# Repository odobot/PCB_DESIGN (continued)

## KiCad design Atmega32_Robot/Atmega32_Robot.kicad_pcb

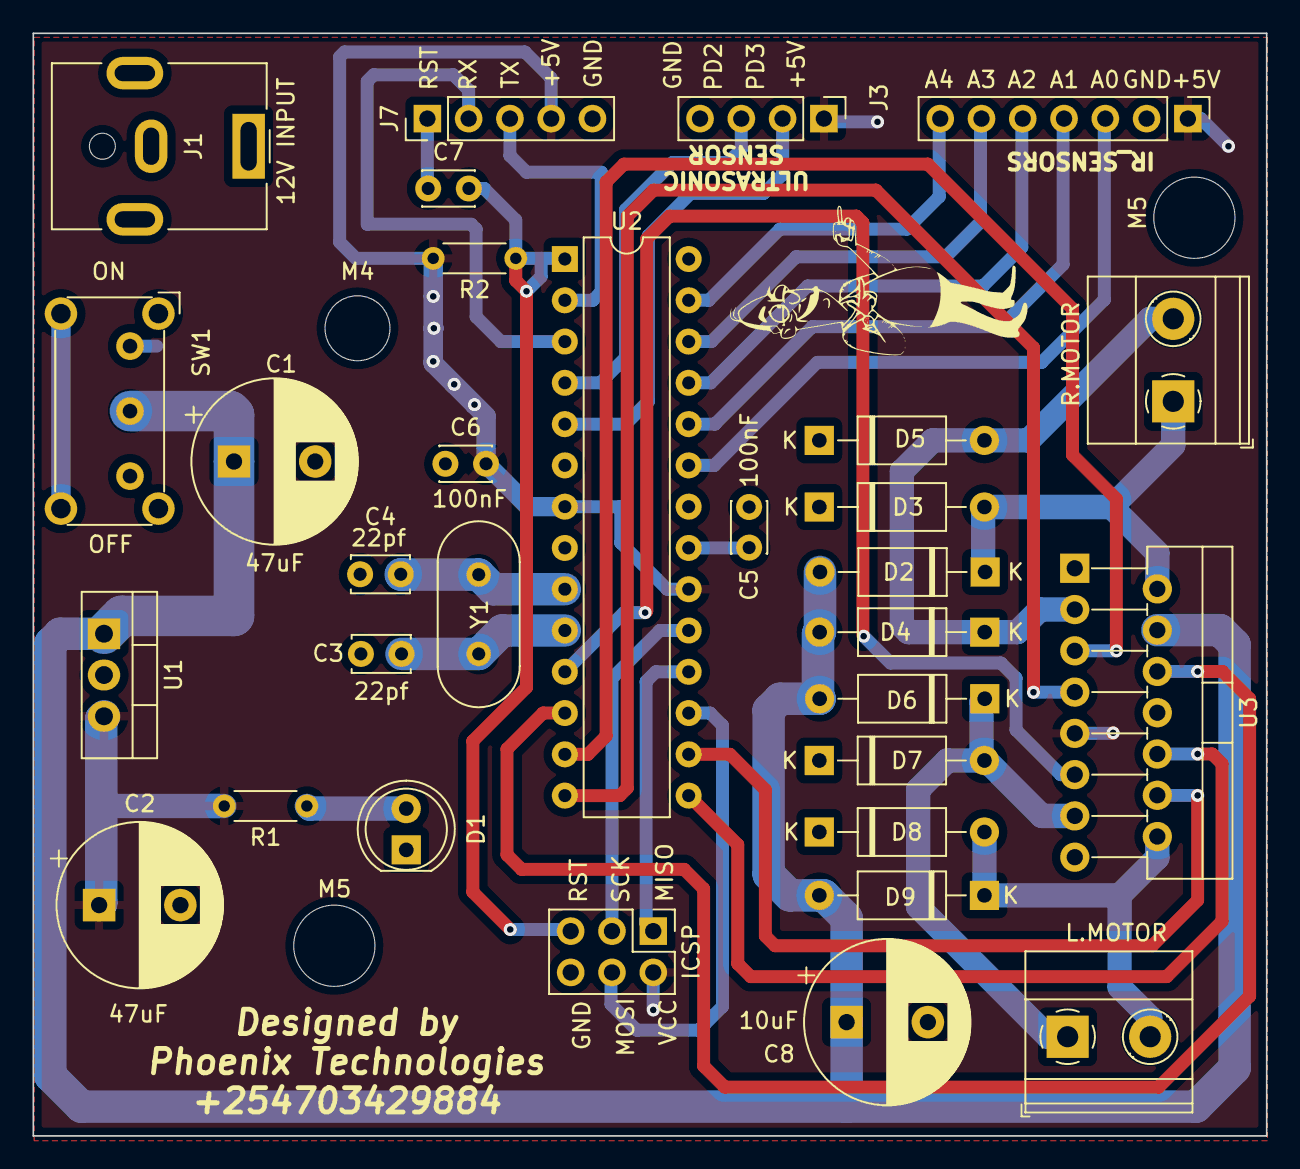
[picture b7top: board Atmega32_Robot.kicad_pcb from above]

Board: 2 copper layers, 75.9 x 67.8 mm, 35 parts (0 on the bottom side), 32 nets.

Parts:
C1, C2: 47uF; CP_Radial_D10.0mm_P5.00mm
C3, C4: 22pf; C_Disc_D3.4mm_W2.1mm_P2.50mm
C5, C6, C7: 100nF; C_Disc_D3.0mm_W2.0mm_P2.50mm
C8: 10uF; CP_Radial_D10.0mm_P5.00mm
Conn_01x07_Male: Conn_01x07_Male; PinHeader_1x07_P2.54mm_Vertical
D1: LED; LED_D5.0mm
D2, D3, D4, D5, D6, D7, D8, D9: DIODE; D_A-405_P10.16mm_Horizontal
G: LOGO; cheech
ICSP: Conn_02x03_Odd_Even; PinHeader_2x03_P2.54mm_Vertical
J1: Barrel_Jack_MountingPin; BarrelJack_CUI_PJ-063AH_Horizontal
J3: Conn_01x04_Male; PinHeader_1x04_P2.54mm_Vertical
J7: Conn_01x05_Male; PinHeader_1x05_P2.54mm_Vertical
L.MOTOR: L.MOTOR; TerminalBlock_Phoenix_MKDS-1,5-2-5.08_1x02_P5.08mm_Horizont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
M4: MountingHole_4mm; MountingHole_2.5mm
M5, M5#2: MountingHole_5mm; MountingHole_2.5mm
R1, R2: 10K; R_Axial_DIN0204_L3.6mm_D1.6mm_P5.08mm_Horizontal
R.MOTOR: R.MOTOR; TerminalBlock_Phoenix_MKDS-1,5-2-5.08_1x02_P5.08mm_Horizont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
SW1: SW_DIP_x01; SW_E-Switch_EG1224_SPDT_Angled
U1: LM78M05_TO220; TO-220-3_Vertical
U2: ATmega328P-P; DIP-28_W7.62mm
U3: L298N; TO-220-15_P2.54x2.54mm_StaggerOdd_Lead4.58mm_Vertical
Y1: 16MHZ; Crystal_HC49-4H_Vertical

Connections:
12V: J1.1, SW1.1
+5V: C2.1, C6.2, Conn_01x07_Male.1, ICSP.2, J3.1, J7.4, R1.2, R2.2, U1.3 (VO), U2.7 (VCC), U2.20 (AVCC), U3.9 (Vss)
+12V: C1.1, C8.1, D2.2 (K), D4.2 (K), D6.2 (K), D9.2 (K), SW1.2, U1.1 (VI), U3.4 (Vs)
A0: Conn_01x07_Male.3, U2.23 (PC0)
A1: Conn_01x07_Male.4, U2.24 (PC1)
A2: Conn_01x07_Male.5, U2.25 (PC2)
A3: Conn_01x07_Male.6, U2.26 (PC3)
A4: Conn_01x07_Male.7, U2.27 (PC4)
ECHO: J3.3, U2.4 (PD2)
EnA: U2.12 (PD6), U3.6 (EnA)
EnB: U2.11 (PD5), U3.11 (EnB)
GND: C2.2, C3.1, C4.1, C5.1, C6.1, C8.2, Conn_01x07_Male.2, D1.1 (K), D3.1 (A), D5.1 (A), D7.1 (A), D8.1 (A), ICSP.6, J1.2, J1.MP (MountPin), J3.4, J7.5, SW1.3, U1.2 (GND), U2.8 (GND), U2.22 (GND), U3.1 (SENSE_A), U3.8 (GND), U3.15 (SENSE_B)
IN1: U2.13 (PD7), U3.5 (IN1)
IN2: U2.14 (PB0), U3.7 (IN2)
IN3: U2.15 (PB1), U3.10 (IN3)
IN4: U2.16 (PB2), U3.12 (IN4)
MISO: ICSP.1, U2.18 (PB4)
MOSI: ICSP.4, U2.17 (PB3)
unnamed: C5.2, U2.21 (AREF)
unnamed: C7.1, J7.1
unnamed: D1.2 (A), R1.1
unnamed: D2.1 (A), D3.2 (K), R.MOTOR.1, U3.2 (OUT1)
unnamed: D4.1 (A), D5.2 (K), R.MOTOR.2, U3.3 (OUT2)
unnamed: D6.1 (A), D7.2 (K), L.MOTOR.1, U3.13 (OUT3)
unnamed: D8.2 (K), D9.1 (A), L.MOTOR.2, U3.14 (OUT4)
PB6: C4.2, U2.9 (XTAL1/PB6), Y1.2
PB7: C3.2, U2.10 (XTAL2/PB7), Y1.1
RESET: C7.2, ICSP.5, R2.1, U2.1 (~RESET/PC6)
RX: J7.2, U2.3 (PD1)
SCK: ICSP.3, U2.19 (PB5)
TRIG: J3.2, U2.5 (PD3)
TX: J7.3, U2.2 (PD0)

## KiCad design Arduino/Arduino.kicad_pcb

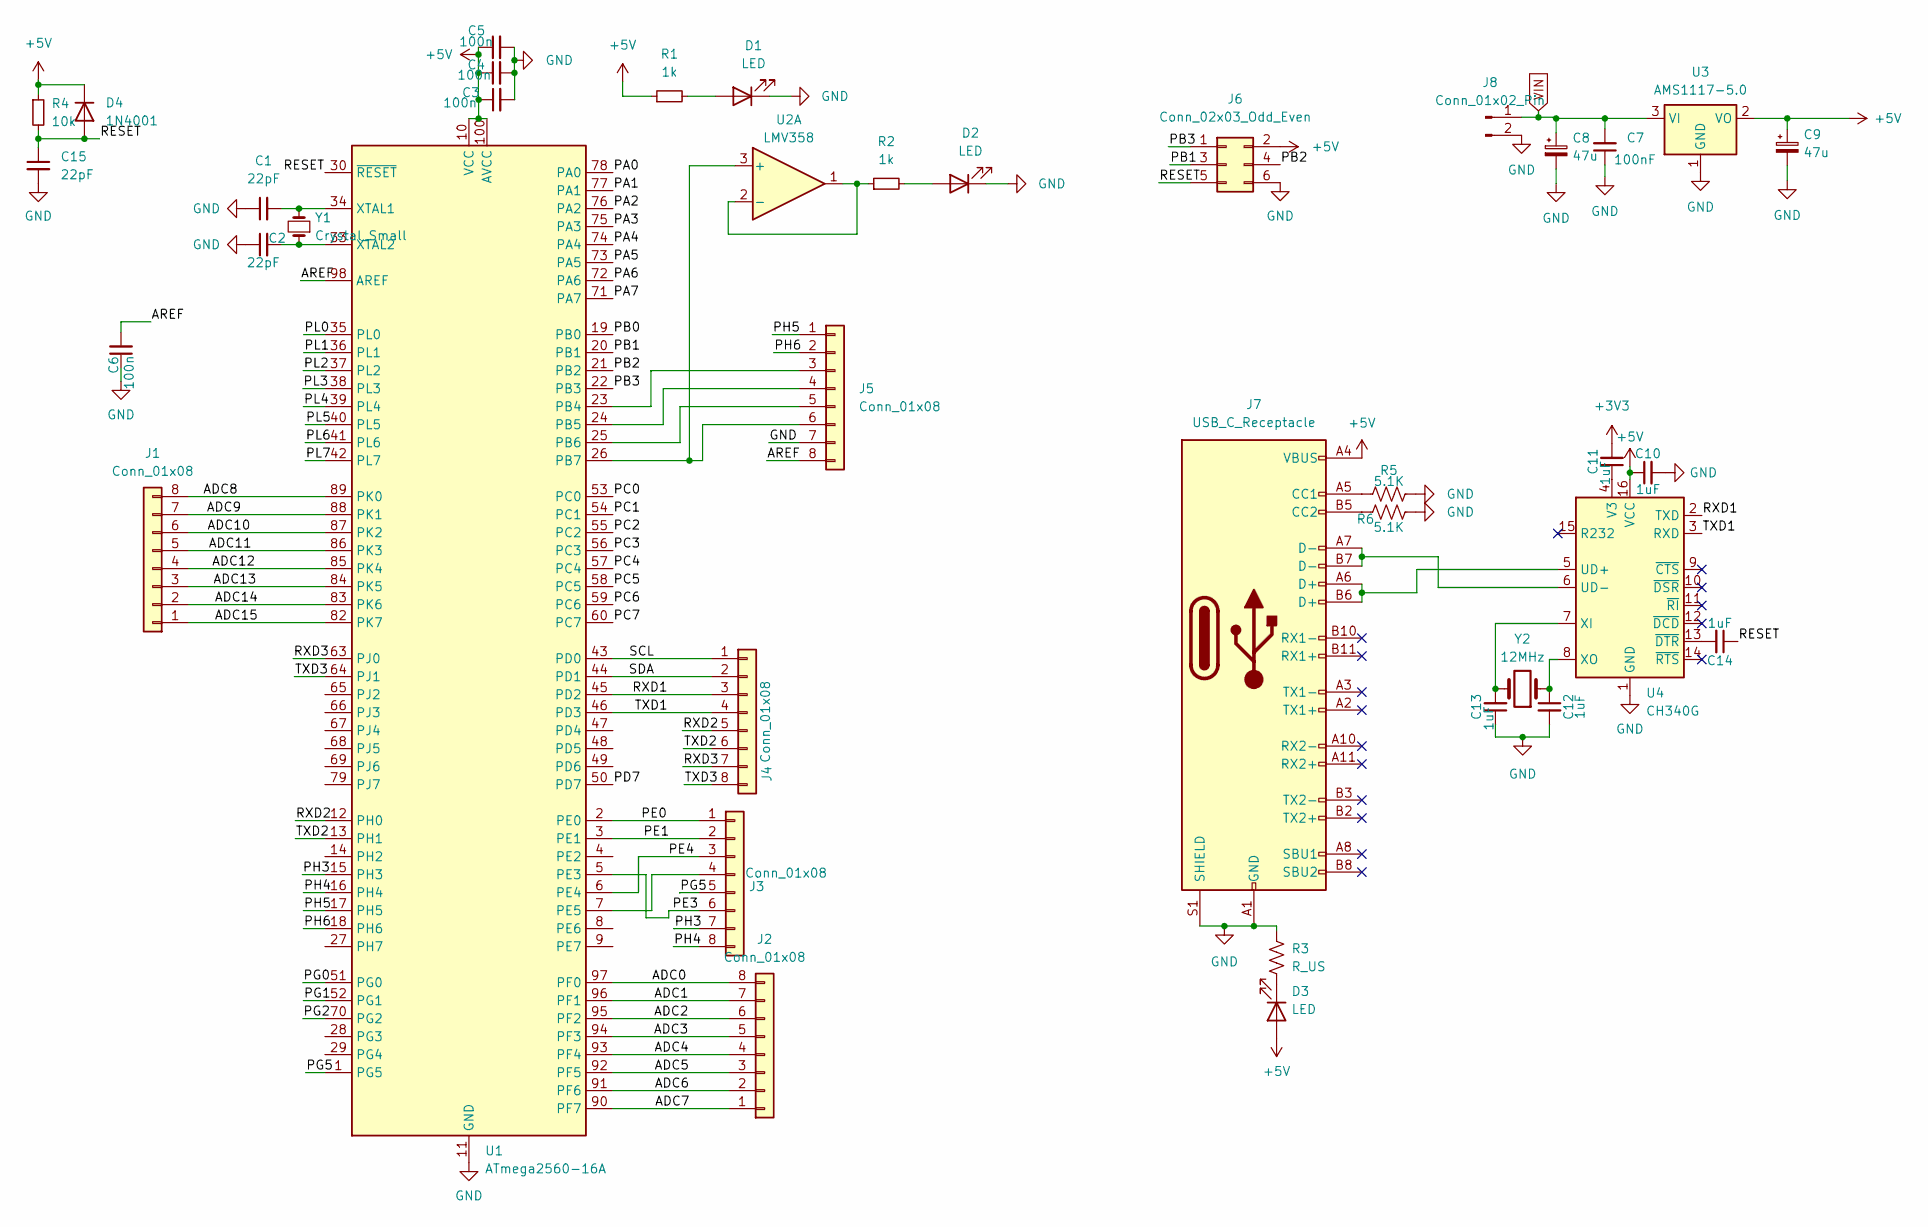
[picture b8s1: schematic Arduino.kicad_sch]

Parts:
C1, C2, C15: 22pF; C_0402_1005Metric
C3, C4, C5, C6: 100n; C_0402_1005Metric
C7: 100nF; C_0402_1005Metric
C8, C9: 47u; CP_Elec_4x3.9
C10, C11, C12, C13, C14: 1uF; C_0402_1005Metric
D1, D2, D3: LED; LED_0402_1005Metric
D4: 1N4001; D_0402_1005Metric
J1, J2, J3, J4, J5: Conn_01x08; PinSocket_1x08_P2.54mm_Vertical
J6: Conn_02x03_Odd_Even; PinSocket_2x03_P2.54mm_Vertical
J7: USB_C_Receptacle; USB_C_Receptacle_Palconn_UTC16-G
J8: Conn_01x02_Pin; JST_XA_B02B-XASK-1_1x02_P2.50mm_Vertical
R1, R2: 1k; R_0402_1005Metric
R3: R_US; R_0402_1005Metric
R4: 10k; R_0402_1005Metric
R5, R6: 5.1K; R_0402_1005Metric
U1: ATmega2560-16A; TQFP-100_14x14mm_P0.5mm
U2: LMV358; DIP-8_W7.62mm_SMDSocket_SmallPads
U3: AMS1117-5.0; SOT-223-3_TabPin2
U4: CH340G; SOIC-16_3.9x9.9mm_P1.27mm
Y1: Crystal_Small; Crystal_SMD_2012-2Pin_2.0x1.2mm
Y2: 12MHz; Crystal_SMD_2012-2Pin_2.0x1.2mm

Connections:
+3V3: C11.2; also elsewhere on the board
+5V: C3.1, C4.1, C5.1, C9.1, C10.1, D3.2 (A), D4.1 (K), J6.2, J7.A4 (VBUS), J7.A9 (VBUS), J7.B4 (VBUS), J7.B9 (VBUS), R1.1, R4.1, U1.10 (VCC), U1.31 (VCC), U1.61 (VCC), U1.80 (VCC), U1.100 (AVCC), U3.2 (VO), U4.16 (VCC)
/ADC0: J2.8, U1.97 (PF0)
/ADC1: J2.7, U1.96 (PF1)
/ADC2: J2.6, U1.95 (PF2)
/ADC3: J2.5, U1.94 (PF3)
/ADC4: J2.4, U1.93 (PF4)
/ADC5: J2.3, U1.92 (PF5)
/ADC6: J2.2, U1.91 (PF6)
/ADC7: J2.1, U1.90 (PF7)
/ADC8: J1.8, U1.89 (PK0)
/ADC9: J1.7, U1.88 (PK1)
/ADC10: J1.6, U1.87 (PK2)
/ADC11: J1.5, U1.86 (PK3)
/ADC12: J1.4, U1.85 (PK4)
/ADC13: J1.3, U1.84 (PK5)
/ADC14: J1.2, U1.83 (PK6)
/ADC15: J1.1, U1.82 (PK7)
/AREF: C6.2, J5.8, U1.98 (AREF)
/PA0: U1.78 (PA0)
/PA1: U1.77 (PA1)
/PA2: U1.76 (PA2)
/PA3: U1.75 (PA3)
/PA4: U1.74 (PA4)
/PA5: U1.73 (PA5)
/PA6: U1.72 (PA6)
/PA7: U1.71 (PA7)
/PB0: U1.19 (PB0)
/PB1: J6.3, U1.20 (PB1)
/PB2: J6.4, U1.21 (PB2)
/PB3: J6.1, U1.22 (PB3)
/PC0: U1.53 (PC0)
/PC1: U1.54 (PC1)
/PC2: U1.55 (PC2)
/PC3: U1.56 (PC3)
/PC4: U1.57 (PC4)
/PC5: U1.58 (PC5)
/PC6: U1.59 (PC6)
/PC7: U1.60 (PC7)
/PD7: U1.50 (PD7)
/PE0: J3.1, U1.2 (PE0)
/PE1: J3.2, U1.3 (PE1)
/PE3: J3.6, U1.5 (PE3)
/PE4: J3.3, U1.6 (PE4)
/PG0: U1.51 (PG0)
/PG1: U1.52 (PG1)
/PG2: U1.70 (PG2)
/PG5: J3.5, U1.1 (PG5)
/PH3: J3.7, U1.15 (PH3)
/PH4: J3.8, U1.16 (PH4)
/PH5: J5.1, U1.17 (PH5)
/PH6: J5.2, U1.18 (PH6)
/PL0: U1.35 (PL0)
/PL1: U1.36 (PL1)
/PL2: U1.37 (PL2)
/PL3: U1.38 (PL3)
/PL4: U1.39 (PL4)
/PL5: U1.40 (PL5)
/PL6: U1.41 (PL6)
/PL7: U1.42 (PL7)
/RESET: C14.1, C15.1, D4.2 (A), J6.5, R4.2, U1.30 (~RESET)
/RXD1: J4.3, U1.45 (PD2), U4.2 (TXD)
/RXD2: J4.5, U1.12 (PH0)
/RXD3: J4.7, U1.63 (PJ0)
/SCL: J4.1, U1.43 (PD0)
/SDA: J4.2, U1.44 (PD1)
/TXD1: J4.4, U1.46 (PD3), U4.3 (RXD)
/TXD2: J4.6, U1.13 (PH1)
/TXD3: J4.8, U1.64 (PJ1)
GND: C1.1, C2.1, C3.2, C4.2, C5.2, C6.1, C7.1, C8.2, C9.2, C10.2, C12.2, C13.1, C15.2, D1.1 (K), D2.1 (K), J5.7, J6.6, J7.A1 (GND), J7.A12 (GND), J7.B1 (GND), J7.B12 (GND), J7.S1 (SHIELD), J8.2, R3.1, R5.2, R6.2, U1.11 (GND), U1.32 (GND), U1.62 (GND), U1.81 (GND), U1.99 (GND), U3.1 (GND), U4.1 (GND); also elsewhere on the board
unnamed: D1.2 (A), R1.2
unnamed: D2.2 (A), R2.2
unnamed: D3.1 (K), R3.2
unnamed: J3.4, U1.7 (PE5)
unnamed: J5.3, U1.23 (PB4)
unnamed: J5.4, U1.24 (PB5)
unnamed: J5.5, U1.25 (PB6)
unnamed: J5.6, U1.26 (PB7), U2.3 (+)
unnamed: J7.A5 (CC1), R5.1
unnamed: J7.B5 (CC2), R6.1
unnamed: C1.2, U1.34 (XTAL1), Y1.2
unnamed: C2.2, U1.33 (XTAL2), Y1.1
unnamed: R2.1, U2.1, U2.2 (-)
unnamed: J7.A6 (D+), J7.B6 (D+), U4.5 (UD+)
unnamed: J7.A7 (D-), J7.B7 (D-), U4.6 (UD-)
unnamed: C11.1, U4.4 (V3)
unnamed: C13.2, U4.7 (XI), Y2.2
unnamed: C12.1, U4.8 (XO), Y2.1
unnamed: C14.2, U4.13 (~DTR)
VIN: C7.2, C8.1, J8.1, U3.3 (VI); also elsewhere on the board

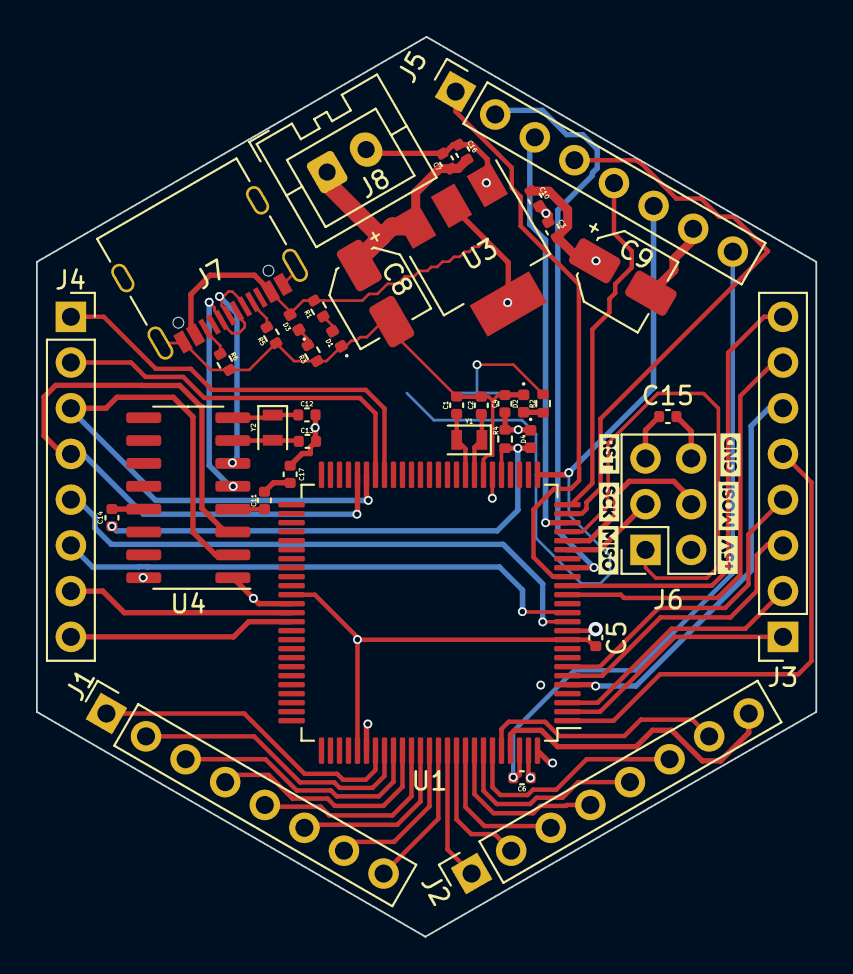
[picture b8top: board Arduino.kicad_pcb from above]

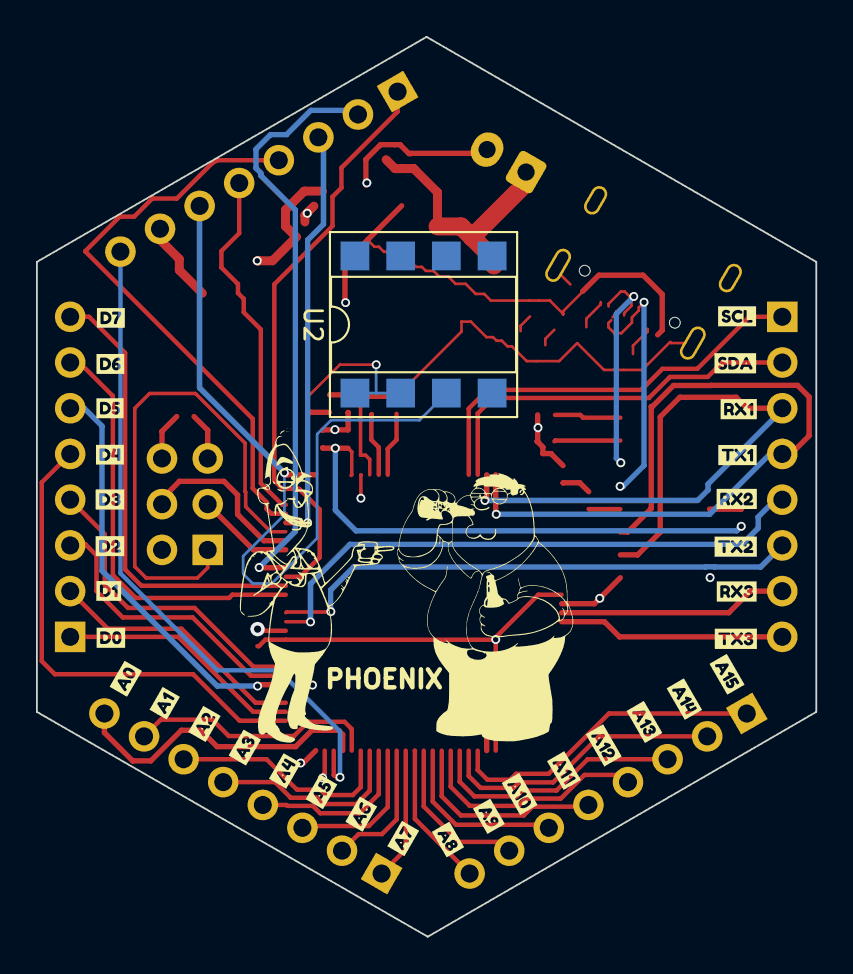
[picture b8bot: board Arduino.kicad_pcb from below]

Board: 4 copper layers, 43.3 x 50.0 mm, 80 parts (34 on the bottom side), 61 nets.

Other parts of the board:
C16, C17: 100nF; C_0402_1005Metric
PHOENIX: LOGO; cheech2
kibuzzard-65DAB4AE: G***; kibuzzard-65DAB4AE
kibuzzard-65DAB4FF: G***; kibuzzard-65DAB4FF
kibuzzard-65DAB5A5: G***; kibuzzard-65DAB5A5
kibuzzard-65DAB5CB: G***; kibuzzard-65DAB5CB
kibuzzard-65DAB5DE: G***; kibuzzard-65DAB5DE
kibuzzard-65DAB5FE: G***; kibuzzard-65DAB5FE
kibuzzard-65DAB6F8: G***; kibuzzard-65DAB6F8
kibuzzard-65DAB7E5: G***; kibuzzard-65DAB7E5
kibuzzard-65DAB9D5: G***; kibuzzard-65DAB9D5
kibuzzard-65DAB9E3: G***; kibuzzard-65DAB9E3
kibuzzard-65DAB9EE: G***; kibuzzard-65DAB9EE
kibuzzard-65DAB58E: G***; kibuzzard-65DAB58E
kibuzzard-65DAB95D: G***; kibuzzard-65DAB95D
kibuzzard-65DAB610: G***; kibuzzard-65DAB610
kibuzzard-65DAB820: G***; kibuzzard-65DAB820
kibuzzard-65DAB856: G***; kibuzzard-65DAB856
kibuzzard-65DABACB: G***; kibuzzard-65DABACB
kibuzzard-65DABAE4: G***; kibuzzard-65DABAE4
kibuzzard-65DABAF2: G***; kibuzzard-65DABAF2
kibuzzard-65DABB0E: G***; kibuzzard-65DABB0E
kibuzzard-65DABB6D: G***; kibuzzard-65DABB6D
kibuzzard-65DABB23: G***; kibuzzard-65DABB23
kibuzzard-65DABB34: G***; kibuzzard-65DABB34
kibuzzard-65DABB77: G***; kibuzzard-65DABB77
kibuzzard-65DABBF1: G***; kibuzzard-65DABBF1
kibuzzard-65DABC2B: G***; kibuzzard-65DABC2B
kibuzzard-65DABC18: G***; kibuzzard-65DABC18
kibuzzard-65DABC40: G***; kibuzzard-65DABC40
kibuzzard-65DABC64: G***; kibuzzard-65DABC64
kibuzzard-65DABC81: G***; kibuzzard-65DABC81
kibuzzard-65DABCAE: G***; kibuzzard-65DABCAE
kibuzzard-65DABCC5: G***; kibuzzard-65DABCC5
kibuzzard-65DABD5B: G***; kibuzzard-65DABD5B
kibuzzard-65DABD9A: G***; kibuzzard-65DABD9A
kibuzzard-65DABD20: G***; kibuzzard-65DABD20
kibuzzard-65DABD37: G***; kibuzzard-65DABD37
kibuzzard-65DABDB1: G***; kibuzzard-65DABDB1
kibuzzard-65DABDCE: G***; kibuzzard-65DABDCE

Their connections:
+3V3: C17.2; also elsewhere on the board
GND: C16.1, C17.1; also elsewhere on the board
VIN: C16.2; also elsewhere on the board

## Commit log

2024-12-31 Add files via upload
    CO2_SENSOR BOARD
2025-01-07 Add files via upload
    Pentaslam pcb
2025-11-10 Add images and sections for LORA and CO2 sensor
